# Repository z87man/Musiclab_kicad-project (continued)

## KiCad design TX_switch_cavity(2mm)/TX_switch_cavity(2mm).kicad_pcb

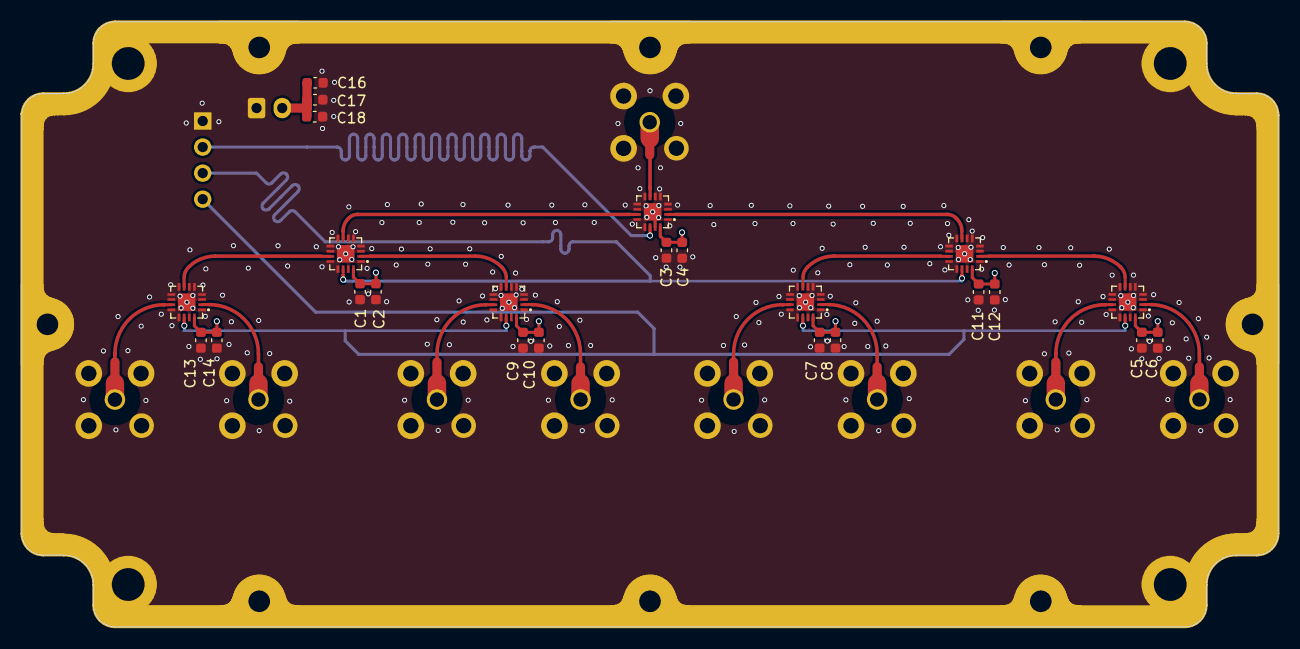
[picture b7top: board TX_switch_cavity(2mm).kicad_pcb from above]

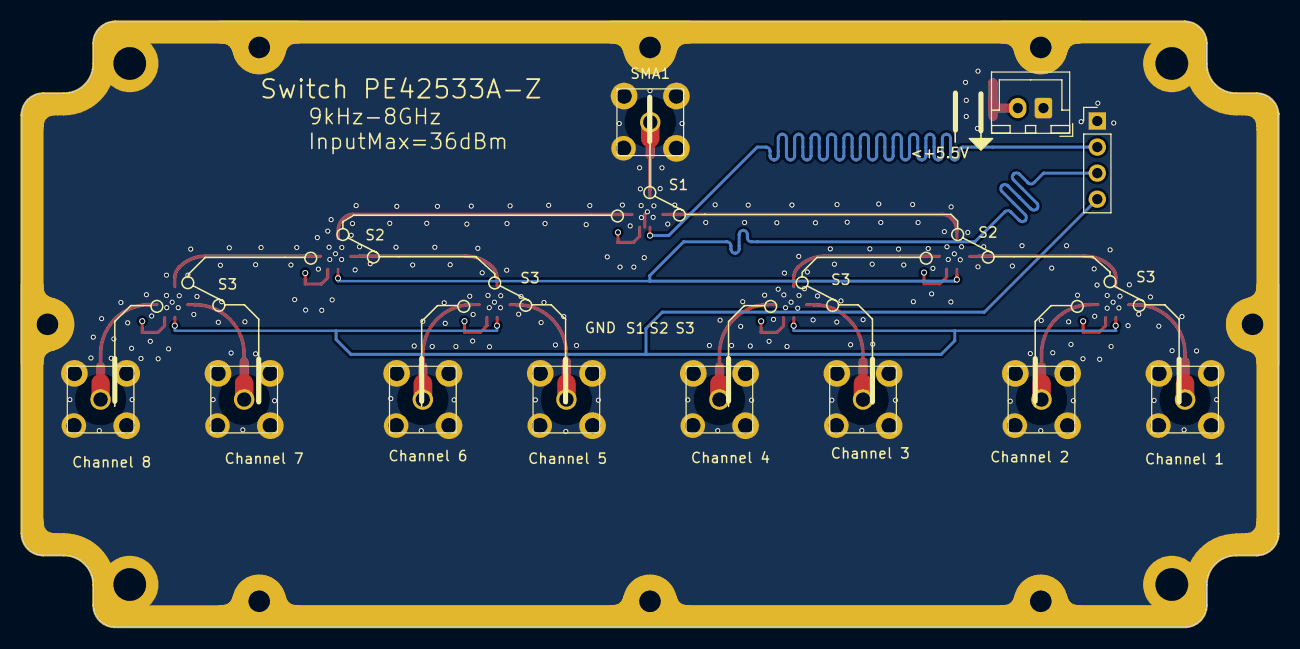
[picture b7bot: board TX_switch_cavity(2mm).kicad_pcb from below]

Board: 4 copper layers, 122.5 x 59.0 mm, 36 parts (11 on the bottom side), 20 nets.

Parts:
C1, C3, C5, C7, C9, C11, C13, C16: 0.1uF; C_0603_1608Metric_revised
C2, C4, C6, C8, C10, C12, C14, C17: 22uF; C_0603_1608Metric_revised
C18: 1uF; C_0603_1608Metric_revised
J2: Conn_01x02_Pin; JST_XH_B2B-XH-A_1x02_P2.50mm_Vertical
J3: Conn_01x04_Pin; PinHeader_1x04_P2.54mm_Vertical
SMA1, SMA2, SMA3, SMA10, SMA11, SMA12, SMA13, SMA14, SMA15: SMA_KHD_Back
U1, U2, U3, U4, U5, U6, U7: Switch_PE42553A-Z; Switch_PE42553A_QFN17N
outline1: Outline_9x4_cavity_20230711

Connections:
/Switch_S3/In: U2.2 (RF1), U4.7 (RFC)
/Switch_S4/In: U2.11 (RF2), U5.7 (RFC)
/Switch_S5/In: U3.2 (RF1), U6.7 (RFC)
/Switch_S6/In: U3.11 (RF2), U7.7 (RFC)
/Switch_cell1/In: SMA1.1, U1.7 (RFC)
/Switch_cell1/Out1: U1.2 (RF1), U2.7 (RFC)
/Switch_cell1/Out2: U1.11 (RF2), U3.7 (RFC)
GND: C1.2, C2.2, C3.2, C4.2, C5.2, C6.2, C7.2, C8.2, C9.2, C10.2, C11.2, C12.2, C13.2, C14.2, C16.2, C17.2, C18.2, J2.1, J3.1, SMA1.2, SMA2.2, SMA3.2, SMA10.2, SMA11.2, SMA12.2, SMA13.2, SMA14.2, SMA15.2, U1.1 (GND), U1.3 (GND), U1.4 (GND), U1.5 (GND), U1.6 (GND), U1.8 (GND), U1.9 (GND), U1.10 (GND), U1.12 (GND), U1.13 (VSS_EXT), U1.15 (LS), U1.EP (GND), U2.1 (GND), U2.3 (GND), U2.4 (GND), U2.5 (GND), U2.6 (GND), U2.8 (GND), U2.9 (GND), U2.10 (GND), U2.12 (GND), U2.13 (VSS_EXT), U2.15 (LS), U2.EP (GND), U3.1 (GND), U3.3 (GND), U3.4 (GND), U3.5 (GND), U3.6 (GND), U3.8 (GND), U3.9 (GND), U3.10 (GND), U3.12 (GND), U3.13 (VSS_EXT), U3.15 (LS), U3.EP (GND), U4.1 (GND), U4.3 (GND), U4.4 (GND), U4.5 (GND), U4.6 (GND), U4.8 (GND), U4.9 (GND), U4.10 (GND), U4.12 (GND), U4.13 (VSS_EXT), U4.15 (LS), U4.EP (GND), U5.1 (GND), U5.3 (GND), U5.4 (GND), U5.5 (GND), U5.6 (GND), U5.8 (GND), U5.9 (GND), U5.10 (GND), U5.12 (GND), U5.13 (VSS_EXT), U5.15 (LS), U5.EP (GND), U6.1 (GND), U6.3 (GND), U6.4 (GND), U6.5 (GND), U6.6 (GND), U6.8 (GND), U6.9 (GND), U6.10 (GND), U6.12 (GND), U6.13 (VSS_EXT), U6.15 (LS), U6.EP (GND), U7.1 (GND), U7.3 (GND), U7.4 (GND), U7.5 (GND), U7.6 (GND), U7.8 (GND), U7.9 (GND), U7.10 (GND), U7.12 (GND), U7.13 (VSS_EXT), U7.15 (LS), U7.EP (GND), outline1.1 (GND)
unnamed: SMA10.1, U4.2 (RF1)
unnamed: SMA11.1, U4.11 (RF2)
unnamed: SMA2.1, U5.2 (RF1)
unnamed: SMA3.1, U5.11 (RF2)
unnamed: SMA12.1, U6.2 (RF1)
unnamed: SMA13.1, U6.11 (RF2)
unnamed: SMA14.1, U7.2 (RF1)
unnamed: SMA15.1, U7.11 (RF2)
Vctr1: J3.2, U1.14 (CTRL)
Vctr2: J3.3, U2.14 (CTRL), U3.14 (CTRL)
Vctr3: J3.4, U4.14 (CTRL), U5.14 (CTRL), U6.14 (CTRL), U7.14 (CTRL)
Vdd: C1.1, C2.1, C3.1, C4.1, C5.1, C6.1, C7.1, C8.1, C9.1, C10.1, C11.1, C12.1, C13.1, C14.1, C16.1, C17.1, C18.1, J2.2, U1.16 (VDD), U2.16 (VDD), U3.16 (VDD), U4.16 (VDD), U5.16 (VDD), U6.16 (VDD), U7.16 (VDD)

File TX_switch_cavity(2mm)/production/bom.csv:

Designator,Footprint,Quantity,Value,LCSC Part #
"C1, C11, C13, C16, C3, C5, C7, C9",0603,8,0.1uF,
"C10, C12, C14, C17, C2, C4, C6, C8",0603,8,22uF,
C18,0603,1,1uF,
J2,JST_XH_B2B-XH-A_1x02_P2.50mm_Vertical,1,Conn_01x02_Pin,
J3,PinHeader_1x04_P2.54mm_Vertical,1,Conn_01x04_Pin,
"SMA1, SMA10, SMA11, SMA12, SMA13, SMA14, SMA15, SMA2, SMA3",SMA_KHD_Back,9,~,
"U1, U2, U3, U4, U5, U6, U7",Switch_PE42553A_QFN17N,7,Switch_PE42553A-Z,
outline1,Outline_9x4_cavity_20230711,1,~,

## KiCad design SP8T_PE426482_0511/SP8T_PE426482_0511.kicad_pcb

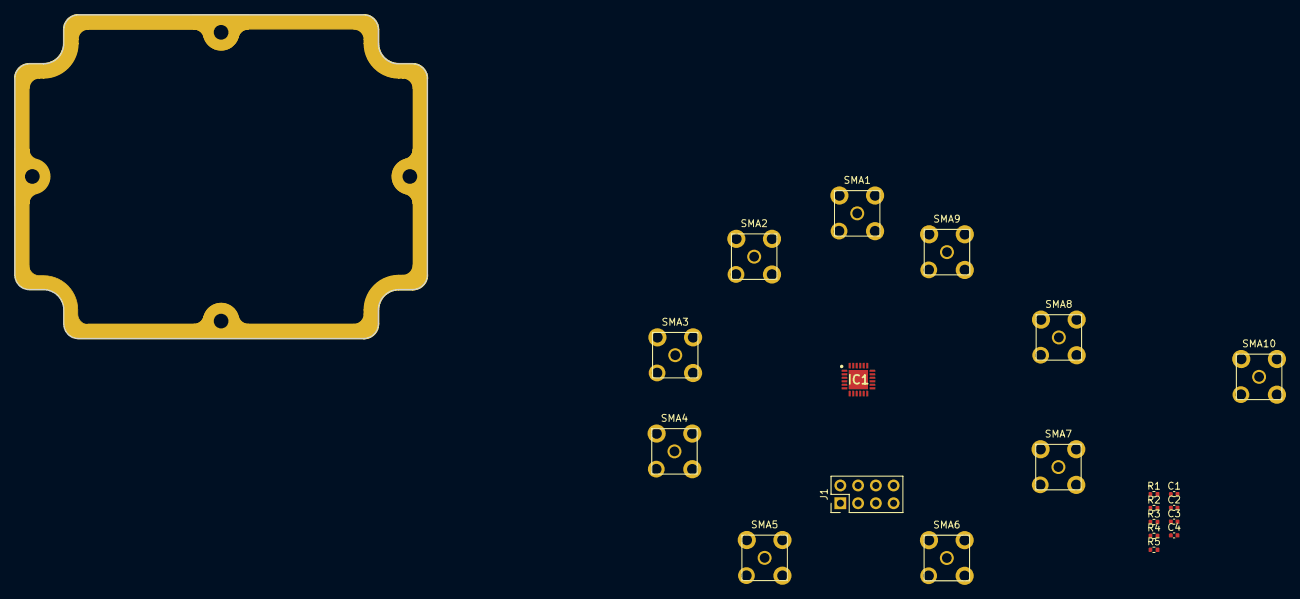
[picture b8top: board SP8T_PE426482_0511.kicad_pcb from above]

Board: 2 copper layers, 22 parts (0 on the bottom side), 17 nets, no tracks yet.

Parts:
C1: 1uF; C_0402_1005Metric
C2: 0.1uF; C_0402_1005Metric
C3: 100 pF; C_0402_1005Metric
C4: 4700 pF; C_0402_1005Metric
IC1: Switch_PE426482A-X; QFN50P400X400X90-25N
J1: Conn_02x04_Odd_Even; PinHeader_2x04_P2.54mm_Vertical
R1: 0; R_0402_1005Metric
R2, R3, R4, R5: 1K; R_0402_1005Metric
SMA1, SMA2, SMA3, SMA4, SMA5, SMA6, SMA7, SMA8, SMA9, SMA10: SMA_KHD_Back
outline1: Outline_4x3_cavity_20240512

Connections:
/Vdd: C1.1, C2.1, C3.1, IC1.8 (VDD), J1.1, J1.3, J1.5, R2.1, SMA10.1
GND: C1.2, C2.2, C3.2, IC1.3 (GND_1), IC1.5 (GND_2), IC1.7 (GND_3), IC1.14 (GND_4), IC1.16 (GND_5), IC1.18 (GND_6), IC1.21 (GND_7), IC1.23 (GND_8), IC1.25 (EP), J1.7, R1.1, R3.1, R4.1, R5.1, SMA1.2, SMA2.2, SMA3.2, SMA4.2, SMA5.2, SMA6.2, SMA7.2, SMA8.2, SMA9.2, SMA10.2
unnamed: C4.2, SMA1.1
unnamed: IC1.1 (LS), R1.2
unnamed: IC1.24 (RF1), SMA2.1
unnamed: IC1.2 (RF2), SMA3.1
unnamed: IC1.4 (RF3), SMA4.1
unnamed: IC1.6 (RF4), SMA5.1
unnamed: IC1.13 (RF5), SMA6.1
unnamed: IC1.15 (RF6), SMA7.1
unnamed: IC1.17 (RF7), SMA8.1
unnamed: IC1.19 (RF8), SMA9.1
unnamed: C4.1, IC1.22 (RFC)
unnamed: IC1.9 (V1), J1.2, R5.2
unnamed: IC1.10 (V2), J1.4, R4.2
unnamed: IC1.11 (V3), J1.6, R3.2
unnamed: IC1.12 (V4), J1.8, R2.2

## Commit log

2025-08-04 将说明文档改为README.md
